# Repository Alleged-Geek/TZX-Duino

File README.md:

# TZX-Duino
My version of the TZX Duino with all components on the component side

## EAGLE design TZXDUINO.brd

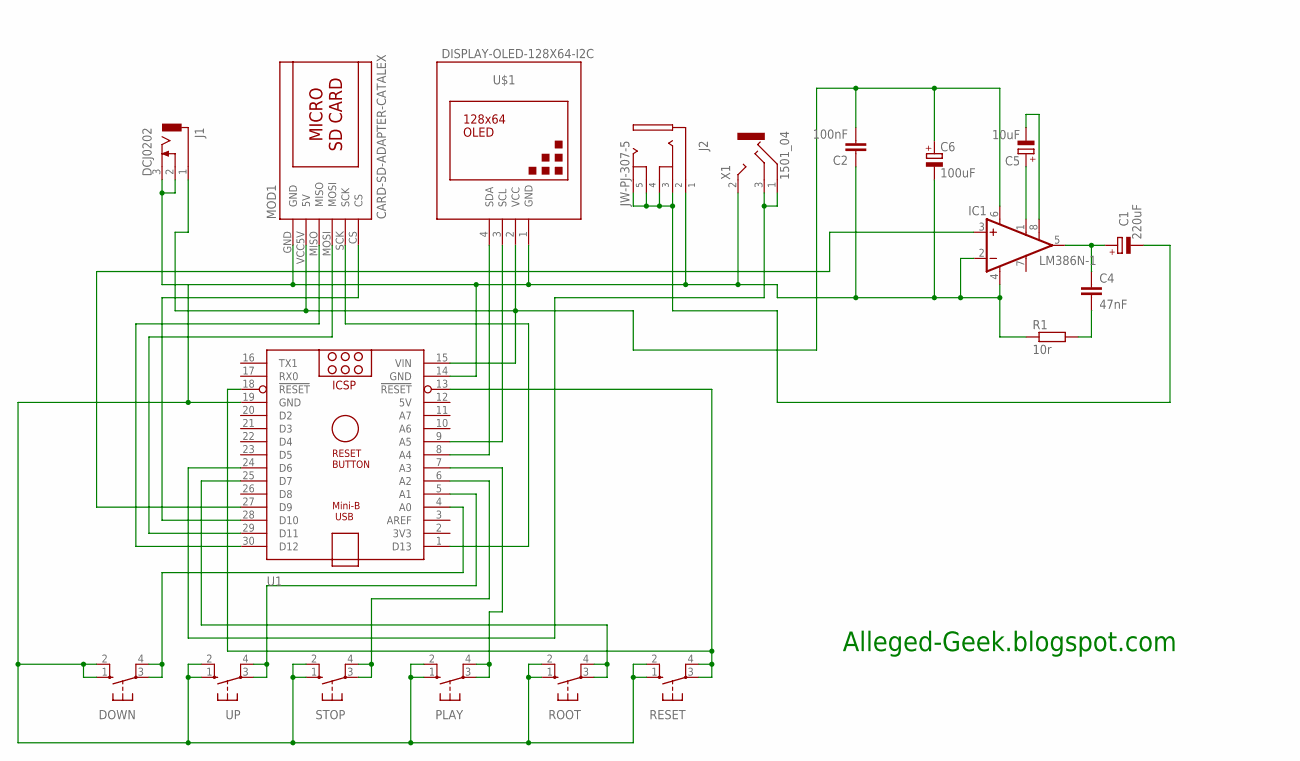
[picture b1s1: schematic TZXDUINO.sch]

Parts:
C1: 220uF; E3,5-8
C2: 100nF; C050-025X075
C4: 47nF; C050-025X075
C5: 10uF; E2,5-5
C6: 100uF; E2,5-5
DOWN: 10-XX; B3F-10XX
IC1: LM386N-1; DIL08
J1: DCJ0202
J2: JW-PJ-307-5
MOD1: CARD-SD-ADAPTER-CATALEX
PLAY: 10-XX; B3F-10XX
R1: 10r; 0207/10
RESET: 10-XX; B3F-10XX
ROOT: 10-XX; B3F-10XX
STOP: 10-XX; B3F-10XX
U1: RGU-ARDUINONANO-SHIELD; ARDUINO_NANO
U$1: DISPLAY-OLED-128X64-I2C
UP: 10-XX; B3F-10XX
X1: 1501_04; 1501_05

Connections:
5V: U1.12 (5V)
unnamed: RESET.3, RESET.4 (P1), U1.13 (!RESET), U1.18 (!RESET)
unnamed: U1.8 (A4), U$1.4 (SDA)
unnamed: C2.2, C6.+, IC1.6 (VS), J1.1, MOD1.VCC5V (5V), U1.15 (VIN), U$1.2 (VCC)
unnamed: MOD1.CS, U1.28 (D10)
unnamed: MOD1.SCK, U1.1 (D13)
unnamed: C1.-, J2.2, J2.3, J2.4, J2.5
unnamed: MOD1.MOSI, U1.29 (D11)
unnamed: U1.9 (A5), U$1.3 (SCL)
unnamed: MOD1.MISO, U1.30 (D12)
unnamed: C2.1, C6.-, DOWN.1 (S), DOWN.2 (S1), IC1.2 (-IN), IC1.4 (GND), J1.2, J1.3, J2.1, MOD1.GND, PLAY.1 (S), PLAY.2 (S1), R1.1, RESET.1 (S), RESET.2 (S1), ROOT.1 (S), ROOT.2 (S1), STOP.1 (S), STOP.2 (S1), U1.14 (GND), U1.19 (GND), U$1.1 (GND), UP.1 (S), UP.2 (S1), X1.2
unnamed: DOWN.3, DOWN.4 (P1), U1.4 (A0)
unnamed: U1.5 (A1), UP.3, UP.4 (P1)
unnamed: STOP.3, STOP.4 (P1), U1.6 (A2)
unnamed: PLAY.3, PLAY.4 (P1), U1.7 (A3)
unnamed: ROOT.3, ROOT.4 (P1), U1.25 (D7)
unnamed: IC1.3 (+IN), U1.27 (D9)
unnamed: C5.+, IC1.1 (GAIN)
unnamed: C1.+, C4.1, IC1.5 (OUT)
unnamed: C4.2, R1.2
unnamed: C5.-, IC1.8 (GAIN)
unnamed: U1.24 (D6), X1.1, X1.3

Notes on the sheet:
Alleged-Geek.blogspot.com

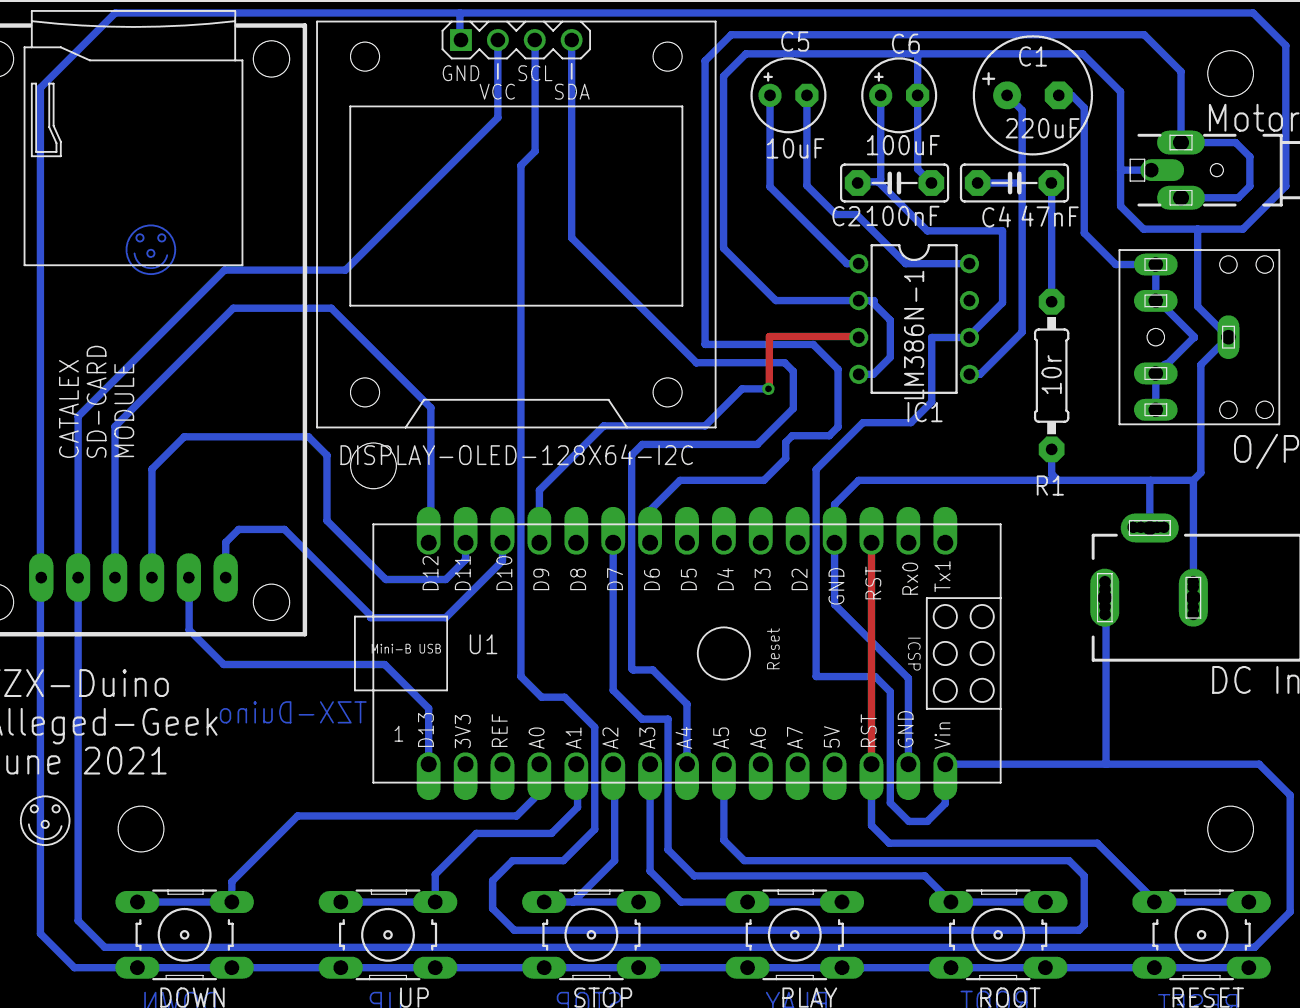
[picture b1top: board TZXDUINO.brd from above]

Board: 2 copper layers, 20 parts (0 on the bottom side), 21 nets.

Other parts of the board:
DRILEGEND: DRILEGEND

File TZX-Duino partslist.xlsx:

TZX Duino - Custom PCB Design by Alleged-Geek |  | Alleged-Geek.blogspot.com
Component | Value | Suppier | Order Code | Quantity | Price | Total Price
C1 | 220uF | Rapid | 11-1541 | 5 | 0.126 | 0.63
C2 | 100nF | Rapid | 10-3260. | 5 | 0.16600000000000001 | 0.83000000000000007
C4 | 47nF | Rapid | 10-3258. | 5 | 0.16800000000000001 | 0.84000000000000008
C5 | 10uF | Rapid | 11-2930. | 5 | 7.4999999999999997E-2 | 0.375
C6 | 100uF | Rapid | 11-3360. | 5 | 5.6000000000000001E-2 | 0.28000000000000003
DOWN | Tactile Switch | Rapid | 78-0625 | 30 | 0.113 | 3.39
UP | Tactile Switch | Rapid | 78-0625 |  |  | 0
PLAY | Tactile Switch | Rapid | 78-0625 |  |  | 0
ROOT | Tactile Switch | Rapid | 78-0625 |  |  | 0
STOP | Tactile Switch | Rapid | 78-0625 |  |  | 0
RESET | Tactile Switch | Rapid | 78-0625 |  |  | 0
IC1 | LM386 | Rapid | 82-0264 | 5 | 0.747 | 3.7349999999999999
J1 | 2.1mm DC Jack Socket | Rapid | 50-3266 | 5 | 0.53900000000000003 | 2.6950000000000003
J2 | 3.5mm Stereo Headphone Jack Socket | Rapid | 20-0137 | 10 | 0.222 | 2.2200000000000002
MOD1 | Micro SD Card Reader with Level Shift | ebay | 274735785686 (5 off) |  | 6.3 | 6.3
R1 | 10Ω | Rapid | 73-0057 | 5 | 9.8000000000000004E-2 | 0.49
U$1 | OLED Display 128x64 12C | ebay | 133467846539 (5 off) |  | 13.27 | 13.27
U1 | Arduino Nano | Amazon.co.uk | B08JY9TC85 (5 off) |  | 18.989999999999998 | 18.989999999999998
X1 | 2.5mm Mono Jack Socket | ebay | 362601963467 (5 off) |  | 2.5 | 2.5
IC Socket | 8 Pin DIL Turned Pin Socket | Rapid | 22-1720 | 5 | 0.311 | 1.5549999999999999
 |  |  |  |  |  | 58.1

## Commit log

2021-08-12 Add files via upload
    There are three files listed, The brd and sch are Eagle files and the Zip file is the gerber files in a zip format for JLPCB
2022-06-12 Add files via upload
    Added the 1.18 firmware which has the modified and correct settings for the OLED screen and SD Card in the userconfig.h tab

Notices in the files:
parts and their libraries:
diy-modules: Released under the Creative Commons Attribution 4.0 International License: http://creativecommons.org/licenses/by/4.0
